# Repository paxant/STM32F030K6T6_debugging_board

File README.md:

# STM32F030K6T6_debugging_board

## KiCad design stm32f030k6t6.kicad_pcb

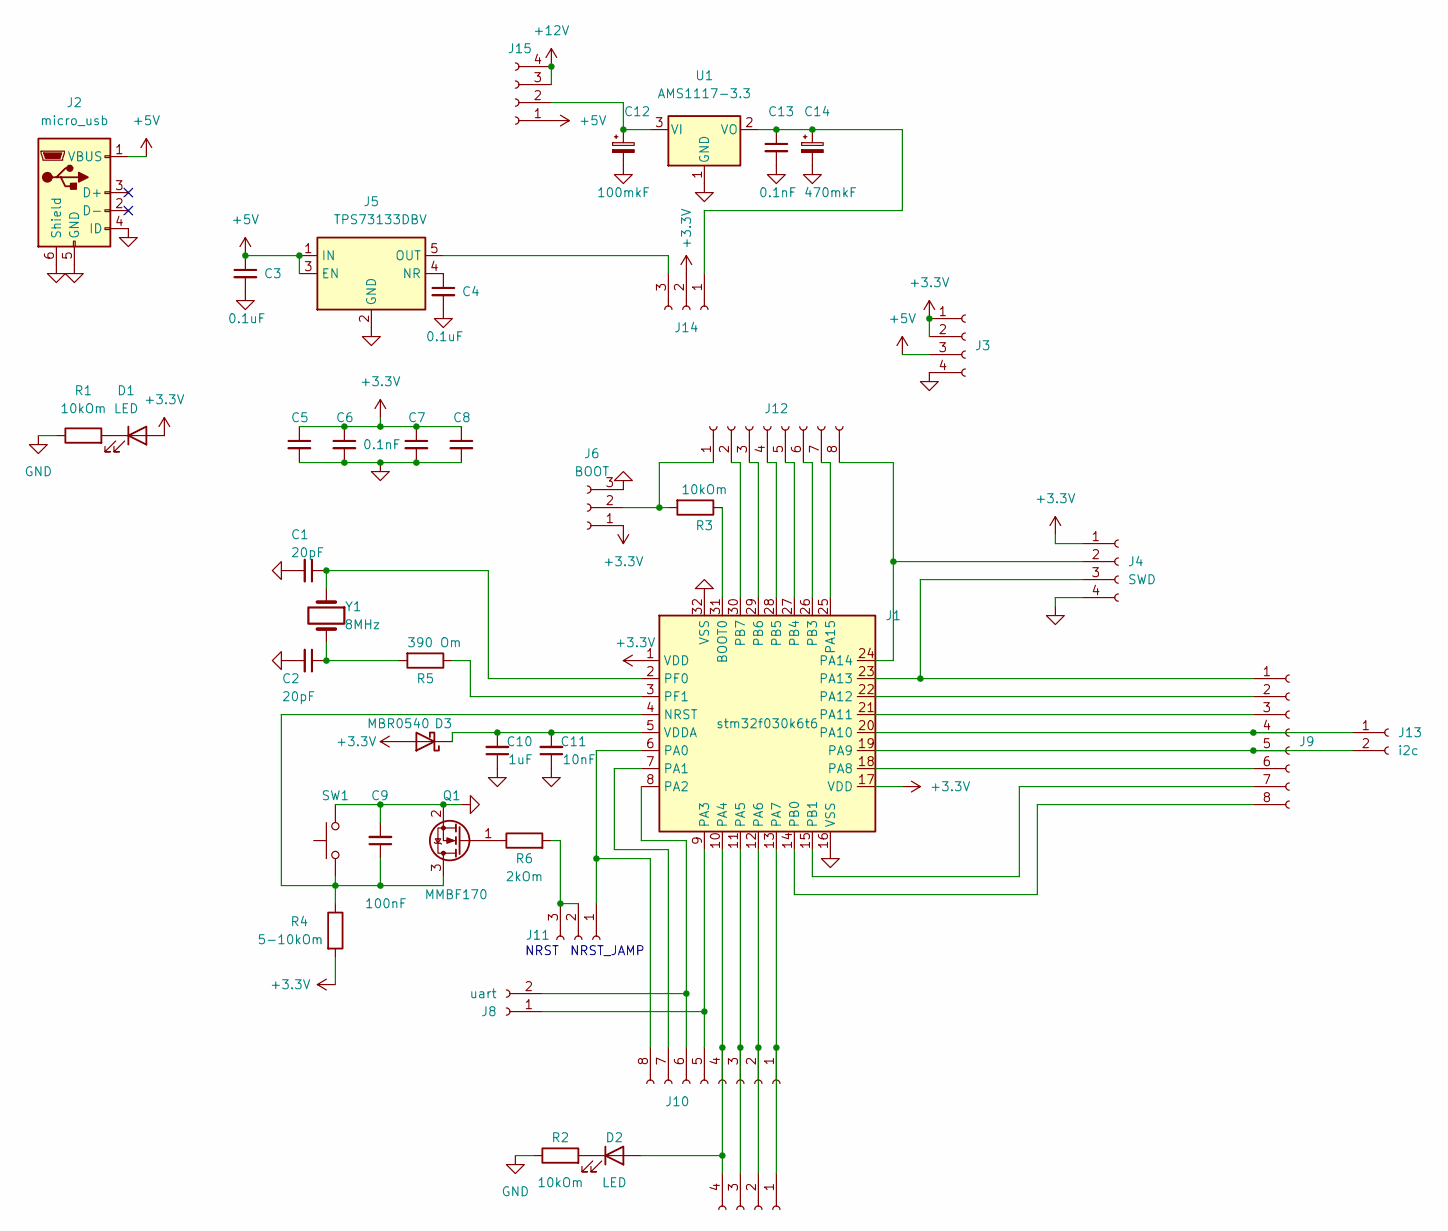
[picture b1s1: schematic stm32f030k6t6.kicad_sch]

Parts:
C1, C2: 20pF; C_0201_0603Metric
C3, C4: 0.1uF; C_0603_1608Metric
C5, C6, C7, C8, C13: 0.1nF; C_0603_1608Metric
C9: 100nF; C_0603_1608Metric
C10: 1uF; C_0603_1608Metric
C11: 10nF; C_0603_1608Metric
C12: 100mkF; CP_Radial_D8.0mm_P3.50mm
C14: 470mkF; CP_Radial_D8.0mm_P3.50mm
D1, D2: LED; LED_0603_1608Metric_Pad1.05x0.95mm_HandSolder
D3: MBR0540; D_SOD-123
J1: stm32f030k6t6; LQFP-32_7x7mm_P0.8mm
J2: micro_usb; USB_Micro-B_Amphenol_10104110_Horizontal
J3, J15: Conn_01x04_Female; PinHeader_1x04_P2.54mm_Vertical
J4: SWD; PinHeader_1x04_P2.54mm_Vertical
J5: TPS73133DBV; SOT-23-5
J6: BOOT; PinHeader_1x03_P2.54mm_Vertical
J7: spi; PinHeader_1x04_P2.54mm_Vertical
J8: uart; PinHeader_1x02_P2.54mm_Vertical
J9, J10: Сделать вместе; PinHeader_1x08_P2.54mm_Vertical
J11: Сделать вместе; PinHeader_1x03_P2.54mm_Vertical
J12: Conn_01x08_Female; PinHeader_1x08_P2.54mm_Vertical
J13: i2c; PinHeader_1x02_P2.54mm_Vertical
J14: Conn_01x03_Female; PinHeader_1x03_P2.54mm_Vertical
Q1: MMBF170; SOT-23
R1, R2: 10kOm; R_0201_0603Metric
R3: 10kOm; R_0603_1608Metric
R4: 5-10kOm; R_0603_1608Metric
R5: 390 Om; R_0603_1608Metric
R6: 2kOm; R_0603_1608Metric
SW1: SW_Push; SW_SPST_FSMSM
U1: AMS1117-3.3; SOT-223-3_TabPin2
Y1: 8MHz; Crystal_HC18-U_Vertical

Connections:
+3V3: C5.1, C6.1, C7.1, C8.1, D1.2 (A), D3.2 (A), J1.1 (VDD), J1.17 (VDD), J3.1, J3.2, J4.1, J6.1, J14.2, R4.2
+5V: C3.1, J2.1 (VBUS), J3.3, J5.1 (IN), J5.3 (EN), J15.1
+12V: J15.3, J15.4
GND: C1.2, C2.2, C3.2, C4.2, C5.2, C6.2, C7.2, C8.2, C9.2, C10.1, C11.1, C12.2, C13.2, C14.2, J1.16 (VSS), J1.32 (VSS), J2.4 (ID), J2.5 (GND), J2.6 (Shield), J3.4, J4.4, J5.2 (GND), J6.3, Q1.2 (S), R1.1, R2.1, SW1.2, U1.1 (GND)
unnamed: C2.1, R5.2, Y1.2
unnamed: D1.1 (K), R1.2
unnamed: D2.2 (A), J1.10 (PA4), J7.4, J10.4
unnamed: D2.1 (K), R2.2
unnamed: C10.2, C11.2, D3.1 (K), J1.5 (VDDA)
unnamed: J1.31 (BOOT0), R3.1
unnamed: C9.1, J1.4 (NRST), Q1.3 (D), R4.1, SW1.1
unnamed: J1.6 (PA0), J10.8, J11.1
unnamed: J1.7 (PA1), J10.7
unnamed: J1.8 (PA2), J8.2, J10.6
unnamed: J1.9 (PA3), J8.1, J10.5
unnamed: J1.11 (PA5), J7.3, J10.3
unnamed: J1.12 (PA6), J7.2, J10.2
unnamed: J1.13 (PA7), J7.1, J10.1
unnamed: J1.18 (PA8), J9.6
unnamed: J1.19 (PA9), J9.5, J13.2
unnamed: J1.20 (PA10), J9.4, J13.1
unnamed: J1.21 (PA11), J9.3
unnamed: J1.22 (PA12), J9.2
unnamed: J1.23 (PA13), J4.3, J9.1
unnamed: J1.24 (PA14), J4.2, J12.8
unnamed: J1.25 (PA15), J12.7
unnamed: J1.14 (PB0), J9.8
unnamed: J1.15 (PB1), J9.7
unnamed: J1.26 (PB3), J12.6
unnamed: J1.27 (PB4), J12.5
unnamed: J1.28 (PB5), J12.4
unnamed: J1.29 (PB6), J12.3
unnamed: J1.30 (PB7), J12.2
unnamed: C1.1, J1.2 (PF0), Y1.1
unnamed: J1.3 (PF1), R5.1
unnamed: C4.1, J5.4 (NR)
unnamed: J11.2, J11.3, R6.2
unnamed: J6.2, J12.1, R3.2
unnamed: C13.1, C14.1, J14.1, U1.2 (VO)
unnamed: J5.5 (OUT), J14.3
unnamed: C12.1, J15.2, U1.3 (VI)
unnamed: Q1.1 (G), R6.1

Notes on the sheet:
NRST_JAMP
NRST

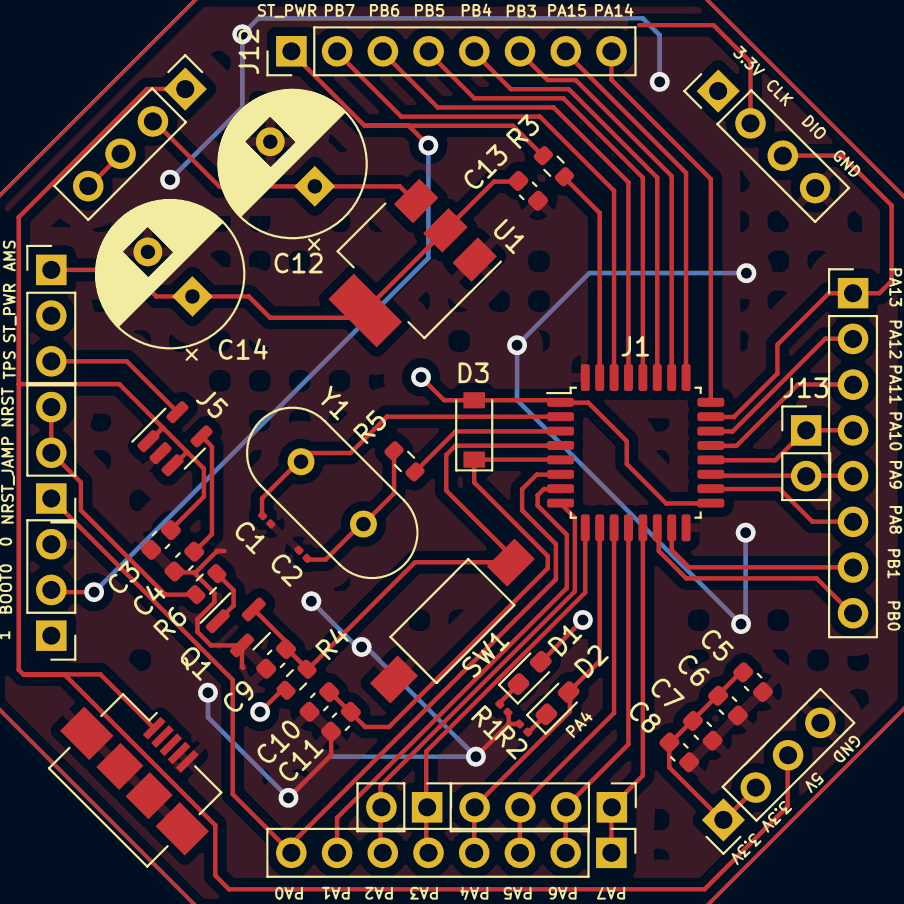
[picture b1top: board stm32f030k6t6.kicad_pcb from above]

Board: 2 copper layers, 42 parts (0 on the bottom side), 42 nets.

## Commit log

2023-08-14 NO COMMIT
2023-08-14 Corrections
    Bug fixes, added firmware for the LED, image
2025-08-11 Добавил гост, чего добру пропадать
